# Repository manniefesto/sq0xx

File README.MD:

# Sq0xx

Squat b0xx.

I've printed and tested V1, there are some fixes in the V2 case files that are untested but should work just fine.

## V1 vs V2
I made a few small changes to the way that the two halves connect.

* Increased the size of the inset to make a tighter fit.
* Moved the magnets closer together.

## 3D Printed parts
* 1 x Top.stl
* 1 x Plate.stl
* 1 x TopLogo.stl
* 1 x Bottom.stl
* 20 x [20mm MX button](https://cdn.thingiverse.com/assets/29/e4/cd/0b/65/20.64mm_Keycap.stl) from the [Fake1](https://www.thingiverse.com/thing:4917086)

## BOM
* PCB, I suggest JLCPCB.
* 20 MX keyboard switches.
* 20 Kailh hot swap sockets.
* Raspberry Pico micro controller.
* M2 Standoffs [Amazon link](https://www.amazon.co.uk/gp/product/B08LDF5SMQ)
* 4 10mm x 3mm magnets [Amazon link](https://www.amazon.co.uk/gp/product/B07QKWBS4S)

## Soldering
All of the components are soldered on to the back of the PCB. The Pico is soldered flat against the board without a socket. I have added break outs for a hardwired GCC cable if required.

## Firmware
Big shout out to Arte for writing some awesome software, [pico-rectangle](https://github.com/JulienBernard3383279/pico-rectangle)

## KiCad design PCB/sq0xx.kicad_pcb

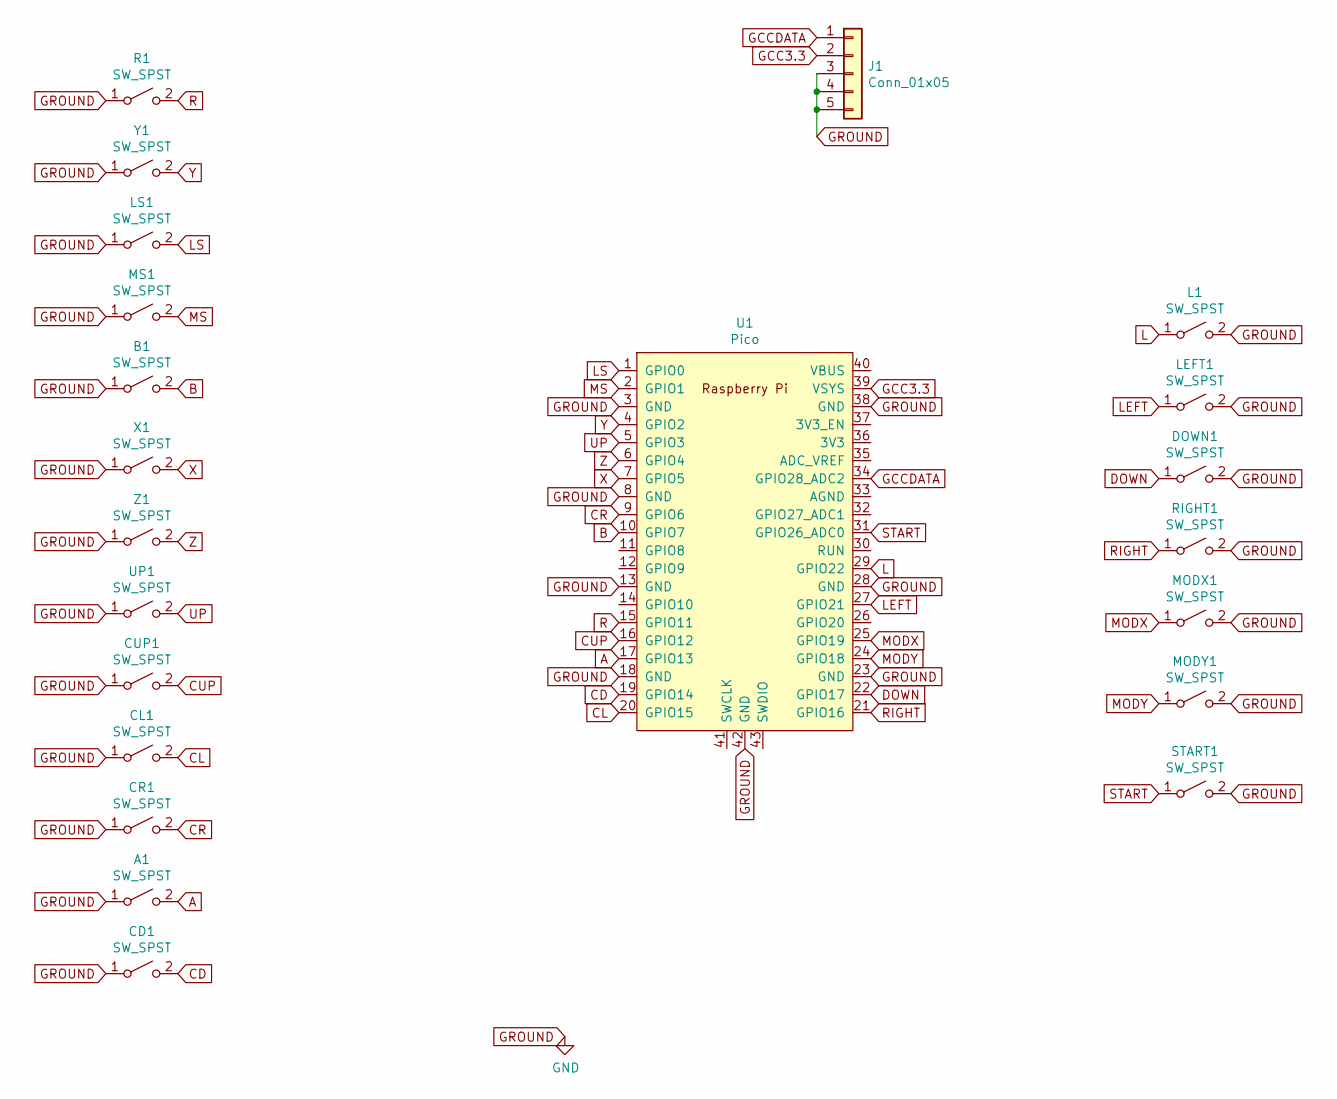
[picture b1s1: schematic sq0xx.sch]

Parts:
A1: SW_SPST; SW_Hotswap_Kailh
B1: SW_SPST; SW_Hotswap_Kailh
CD1: SW_SPST; SW_Hotswap_Kailh
CL1: SW_SPST; SW_Hotswap_Kailh
CR1: SW_SPST; SW_Hotswap_Kailh
CUP1: SW_SPST; SW_Hotswap_Kailh
DOWN1: SW_SPST; SW_Hotswap_Kailh
J1: Conn_01x05; PinHeader_1x05_P2.00mm_Vertical
L1: SW_SPST; SW_Hotswap_Kailh
LEFT1: SW_SPST; SW_Hotswap_Kailh
LS1: SW_SPST; SW_Hotswap_Kailh
MODX1: SW_SPST; SW_Hotswap_Kailh
MODY1: SW_SPST; SW_Hotswap_Kailh
MS1: SW_SPST; SW_Hotswap_Kailh
R1: SW_SPST; SW_Hotswap_Kailh
RIGHT1: SW_SPST; SW_Hotswap_Kailh
START1: SW_SPST; SW_Hotswap_Kailh
U1: Pico; RPi_Pico_SMD_TH
UP1: SW_SPST; SW_Hotswap_Kailh
X1: SW_SPST; SW_Hotswap_Kailh
Y1: SW_SPST; SW_Hotswap_Kailh
Z1: SW_SPST; SW_Hotswap_Kailh

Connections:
A: A1.2 (B), U1.17 (GPIO13)
B: B1.2 (B), U1.10 (GPIO7)
CD: CD1.2 (B), U1.19 (GPIO14)
CL: CL1.2 (B), U1.20 (GPIO15)
CR: CR1.2 (B), U1.9 (GPIO6)
CUP: CUP1.2 (B), U1.16 (GPIO12)
DOWN: DOWN1.1 (A), U1.22 (GPIO17)
GCC3.3: J1.2, U1.39 (VSYS)
GCCDATA: J1.1, U1.34 (GPIO28_ADC2)
GROUND: A1.1 (A), B1.1 (A), CD1.1 (A), CL1.1 (A), CR1.1 (A), CUP1.1 (A), DOWN1.2 (B), J1.3, J1.4, J1.5, L1.2 (B), LEFT1.2 (B), LS1.1 (A), MODX1.2 (B), MODY1.2 (B), MS1.1 (A), R1.1 (A), RIGHT1.2 (B), START1.2 (B), U1.3 (GND), U1.8 (GND), U1.13 (GND), U1.18 (GND), U1.23 (GND), U1.28 (GND), U1.38 (GND), U1.42 (GND), UP1.1 (A), X1.1 (A), Y1.1 (A), Z1.1 (A)
L: L1.1 (A), U1.29 (GPIO22)
LEFT: LEFT1.1 (A), U1.27 (GPIO21)
LS: LS1.2 (B), U1.1 (GPIO0)
MODX: MODX1.1 (A), U1.25 (GPIO19)
MODY: MODY1.1 (A), U1.24 (GPIO18)
MS: MS1.2 (B), U1.2 (GPIO1)
R: R1.2 (B), U1.15 (GPIO11)
RIGHT: RIGHT1.1 (A), U1.21 (GPIO16)
START: START1.1 (A), U1.31 (GPIO26_ADC0)
UP: U1.5 (GPIO3), UP1.2 (B)
X: U1.7 (GPIO5), X1.2 (B)
Y: U1.4 (GPIO2), Y1.2 (B)
Z: U1.6 (GPIO4), Z1.2 (B)

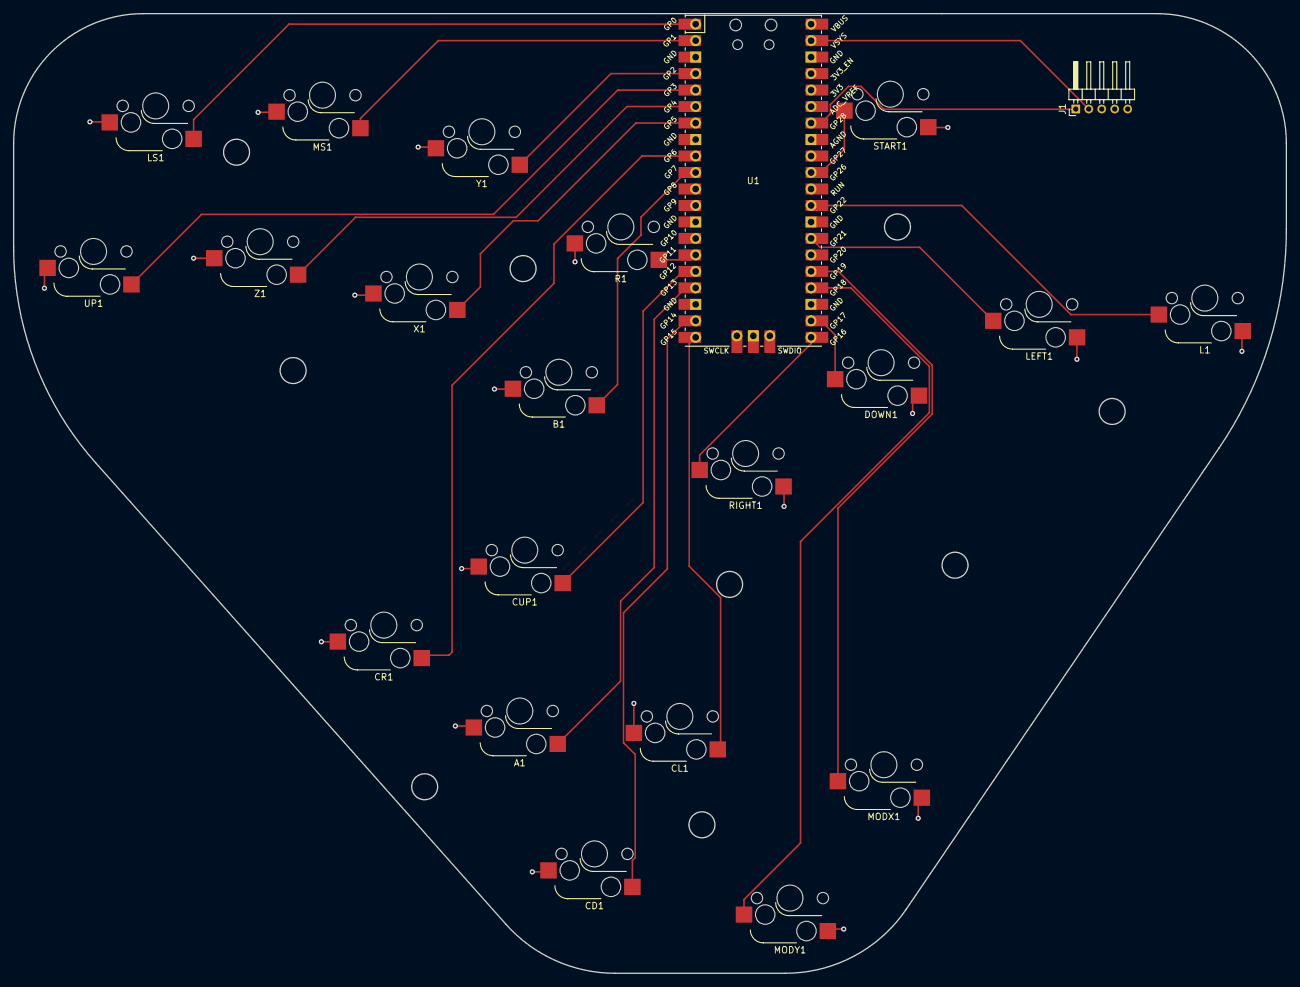
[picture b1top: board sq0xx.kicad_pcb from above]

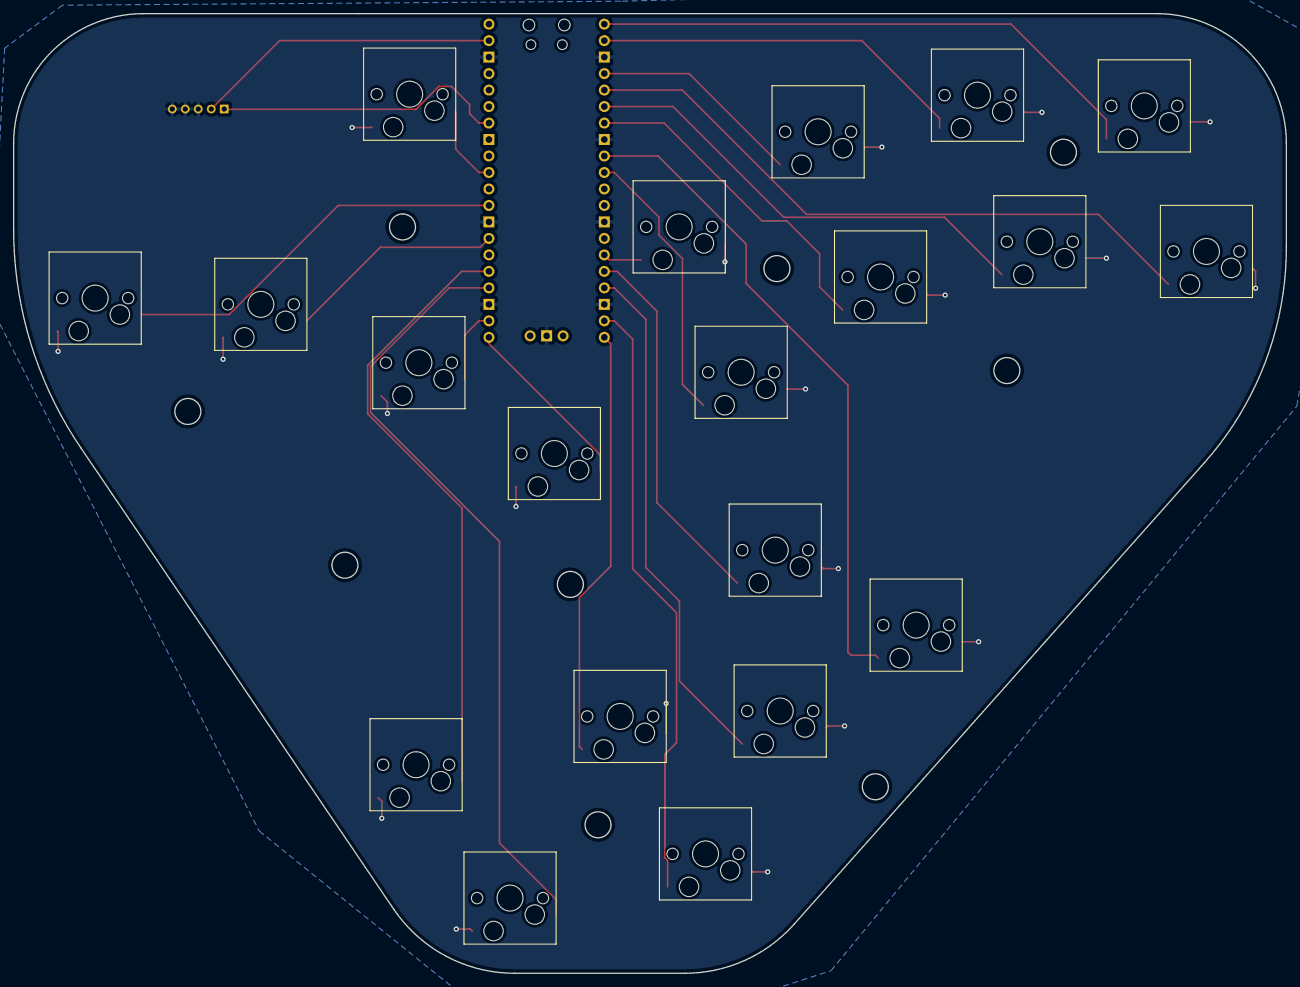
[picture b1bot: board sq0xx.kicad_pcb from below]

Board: 2 copper layers, 196.1 x 147.9 mm, 22 parts (20 on the bottom side), 23 nets.

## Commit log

2021-12-13 Added draft PCB files
2021-12-13 Folder changes and lots of work
2022-01-04 Fixed missing grounds
2022-01-04 Added case files and readme
2022-01-04 fixed link
2022-01-04 added logo
